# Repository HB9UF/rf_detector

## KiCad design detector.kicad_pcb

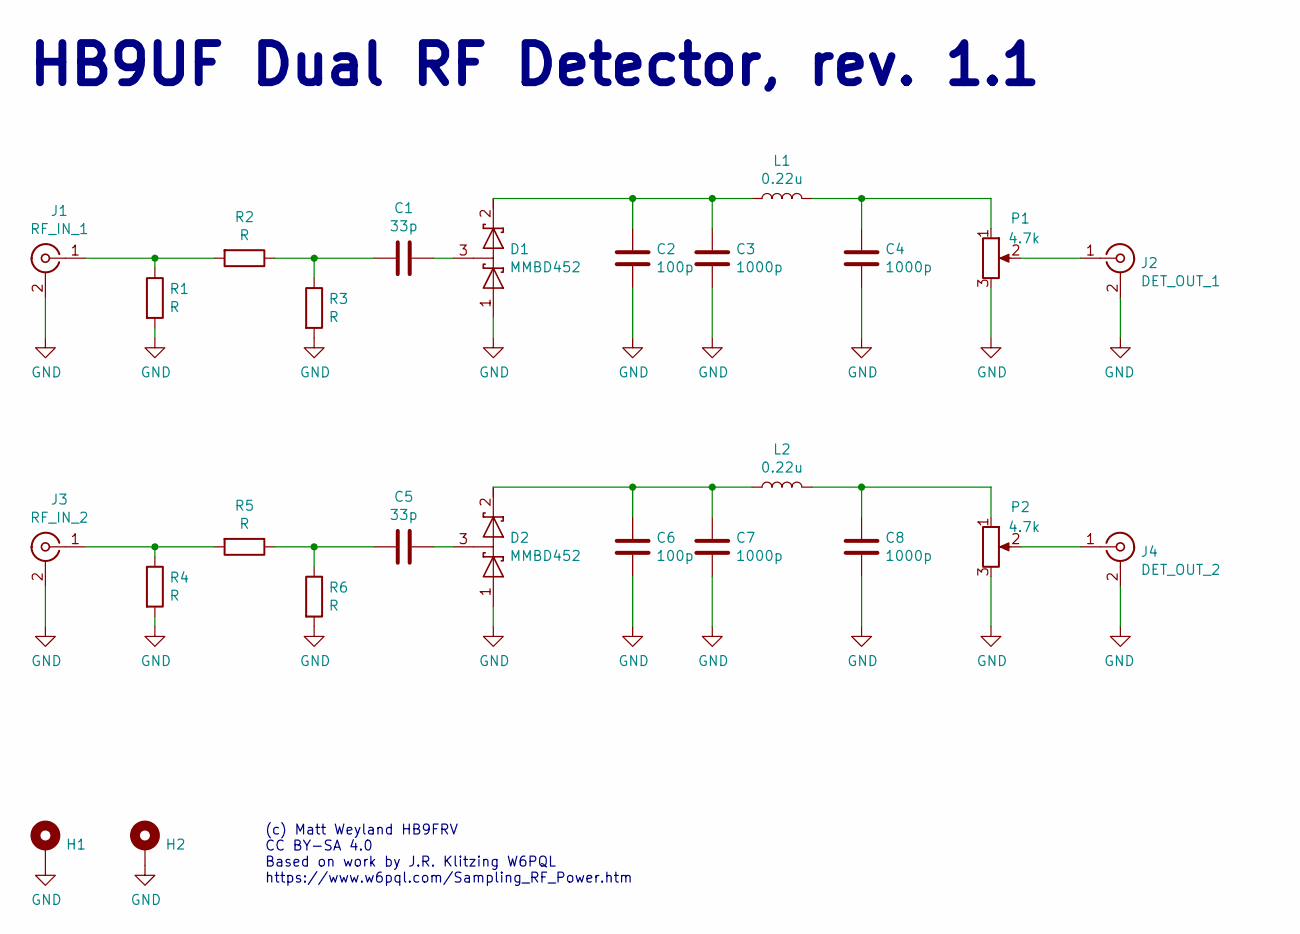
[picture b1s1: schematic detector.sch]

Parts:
C1, C5: 33p; C_1206_3216Metric_Pad1.42x1.75mm_HandSolder
C2, C6: 100p; C_1206_3216Metric_Pad1.42x1.75mm_HandSolder
C3, C4, C7, C8: 1000p; C_1206_3216Metric_Pad1.42x1.75mm_HandSolder
D1, D2: MMBD452; SOT-23
H1, H2: MountingHole_Pad; MountingHole_3.2mm_M3_Pad
J1: RF_IN_1; SMA_Amphenol_901-144_Vertical
J2: DET_OUT_1; SMA_Amphenol_901-144_Vertical
J3: RF_IN_2; SMA_Amphenol_901-144_Vertical
J4: DET_OUT_2; SMA_Amphenol_901-144_Vertical
L1, L2: 0.22u; L_0805_2012Metric_Pad1.15x1.40mm_HandSolder
P1, P2: 4.7k; Potentiometer_Bourns_3296W_Vertical
R1, R2, R3, R4, R5, R6: R; R_1206_3216Metric_Pad1.42x1.75mm_HandSolder

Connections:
GND: C2.2, C3.2, C4.2, C6.2, C7.2, C8.2, D1.1 (A), D2.1 (A), H1.1, H2.1, J1.2 (Ext), J2.2 (Ext), J3.2 (Ext), J4.2 (Ext), P1.3, P2.3, R1.2, R3.2, R4.2, R6.2
unnamed: C1.1, D1.3 (common)
unnamed: C1.2, R2.1, R3.1
unnamed: C2.1, C3.1, D1.2 (K), L1.1
unnamed: C4.1, L1.2, P1.1
unnamed: C5.1, D2.3 (common)
unnamed: C5.2, R5.1, R6.1
unnamed: C6.1, C7.1, D2.2 (K), L2.1
unnamed: C8.1, L2.2, P2.1
unnamed: J1.1 (In), R1.1, R2.2
unnamed: J2.1 (In), P1.2
unnamed: J3.1 (In), R4.1, R5.2
unnamed: J4.1 (In), P2.2

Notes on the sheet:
HB9UF Dual RF Detector, rev. 1.1
(c) Matt Weyland HB9FRV CC BY-SA 4.0 Based on work by J.R. Klitzing W6PQL https://www.w6pql.com/Sampling_RF_Power.htm

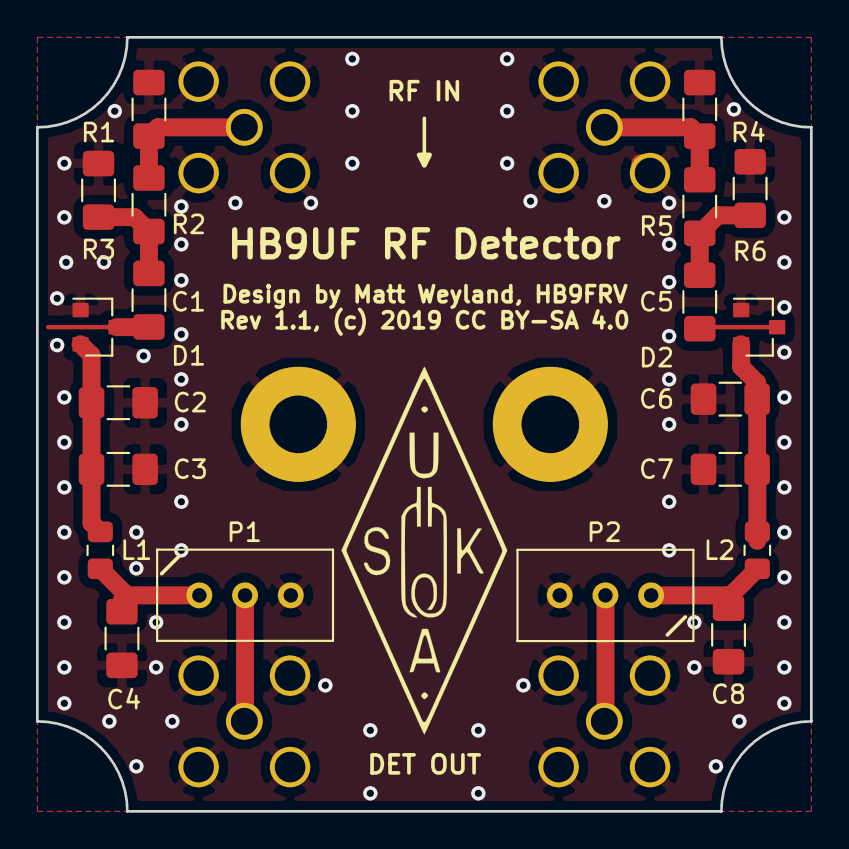
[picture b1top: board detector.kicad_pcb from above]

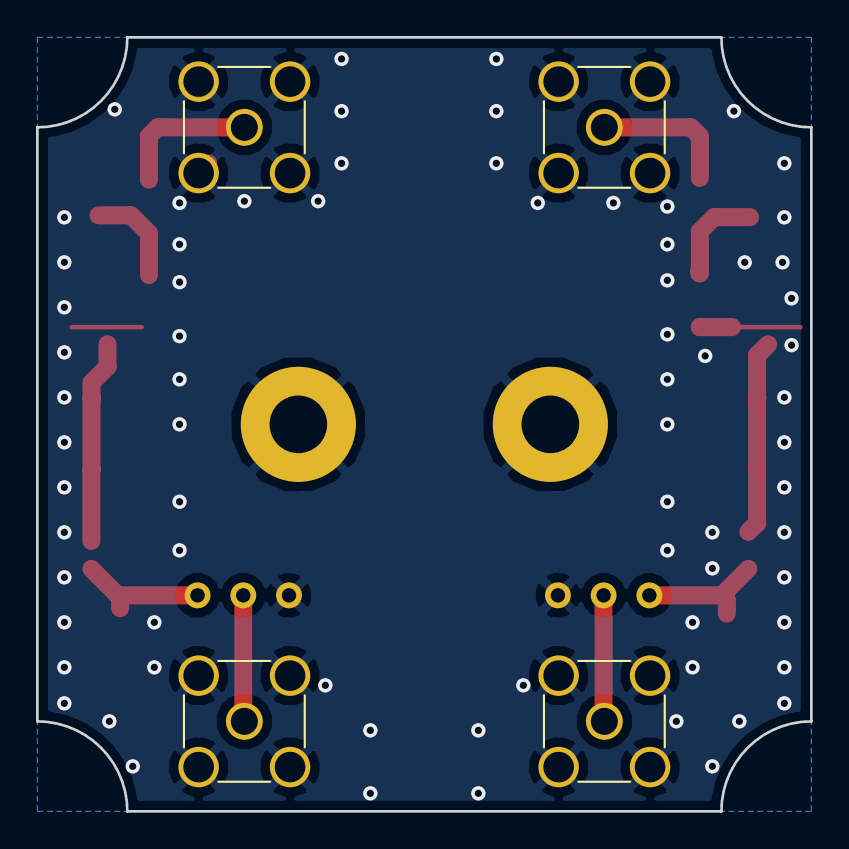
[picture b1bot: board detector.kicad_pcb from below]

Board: 2 copper layers, 43.0 x 43.0 mm, 26 parts (4 on the bottom side), 13 nets.

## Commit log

2019-04-19 Initial commit of rev. 1.0
2019-04-19 Switch SMA footprint from edge mount to vertical in schematic
2019-04-19 Correct P2 footprint in schematic
2019-04-19 Reduce size of PCB to fit in RND 455-00853 case with new footprints
2019-04-20 Replaced HB9UF silk logo with thinner version
2019-04-20 Bumping revision to 1.1, put CC license on silk
2019-04-20 Last minute fix for rev. 1.1: pin 1 mark for P2 was wrong
2019-04-28 Adding attenuation table for resistor values
2019-05-14 Adding pptx file of final flyer for the 2019 event (Rütihof)

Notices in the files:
detector.kicad_pcb:
Rev 1.1, (c) 2019 CC BY-SA 4.0
